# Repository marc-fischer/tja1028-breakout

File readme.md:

# TJA1028 Breakout board

This breakout board provides a simple method to use a TJA1028T LIN transceiver with any microcontroller or development board (ie. Arduino, NodeMCU)

## Picture of the Board

## Schematics

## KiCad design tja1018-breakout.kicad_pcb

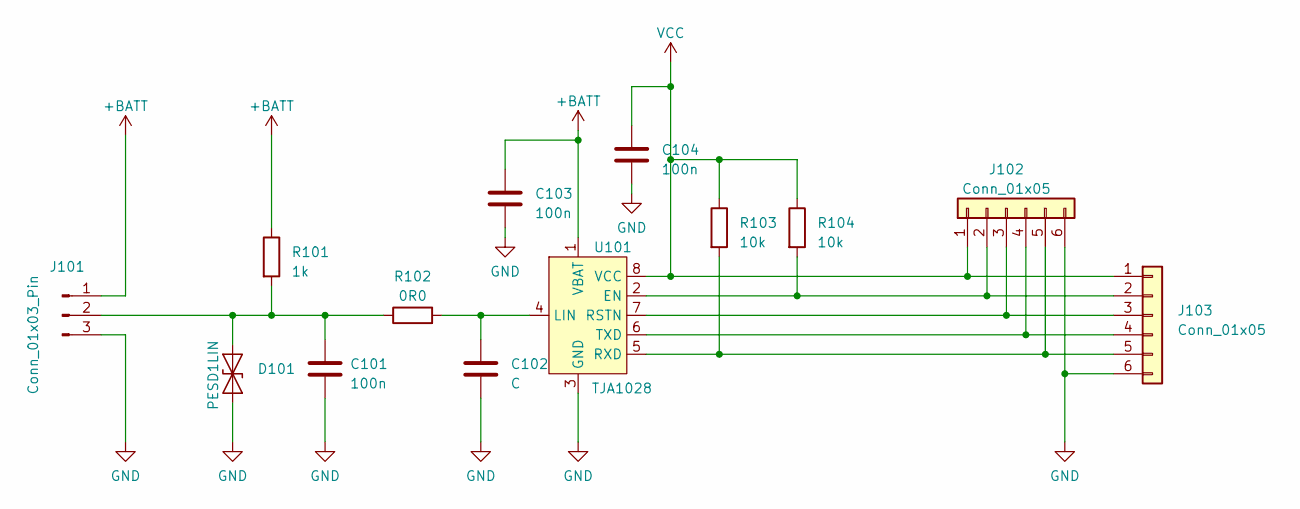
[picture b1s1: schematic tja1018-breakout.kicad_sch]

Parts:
C101, C103, C104: 100n; C_0603_1608Metric
C102: C; C_0603_1608Metric
D101: PESD1LIN; D_SMA-SMB_Universal_Handsoldering
J101: Conn_01x03_Pin; TerminalBlock_bornier-3_P5.08mm
J102, J103: Conn_01x05; PinHeader_1x06_P2.54mm_Vertical
R101: 1k; R_0603_1608Metric
R102: 0R0; R_0603_1608Metric
R103, R104: 10k; R_0603_1608Metric
U101: TJA1028; SO-8_3.9x4.9mm_P1.27mm

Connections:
+BATT: C103.1, J101.1, R101.1, U101.1 (VBAT)
GND: C101.2, C102.2, C103.2, C104.2, D101.1 (A1), J101.3, J102.6, J103.6, U101.3 (GND)
unnamed: C101.1, D101.2 (A2), J101.2, R101.2, R102.1
unnamed: J102.2, J103.2, R104.2, U101.2 (EN)
unnamed: J102.3, J103.3, U101.7 (RSTN)
unnamed: J102.4, J103.4, U101.6 (TXD)
unnamed: J102.5, J103.5, R103.2, U101.5 (RXD)
unnamed: C102.1, R102.2, U101.4 (LIN)
VCC: C104.1, J102.1, J103.1, R103.1, R104.1, U101.8 (VCC)

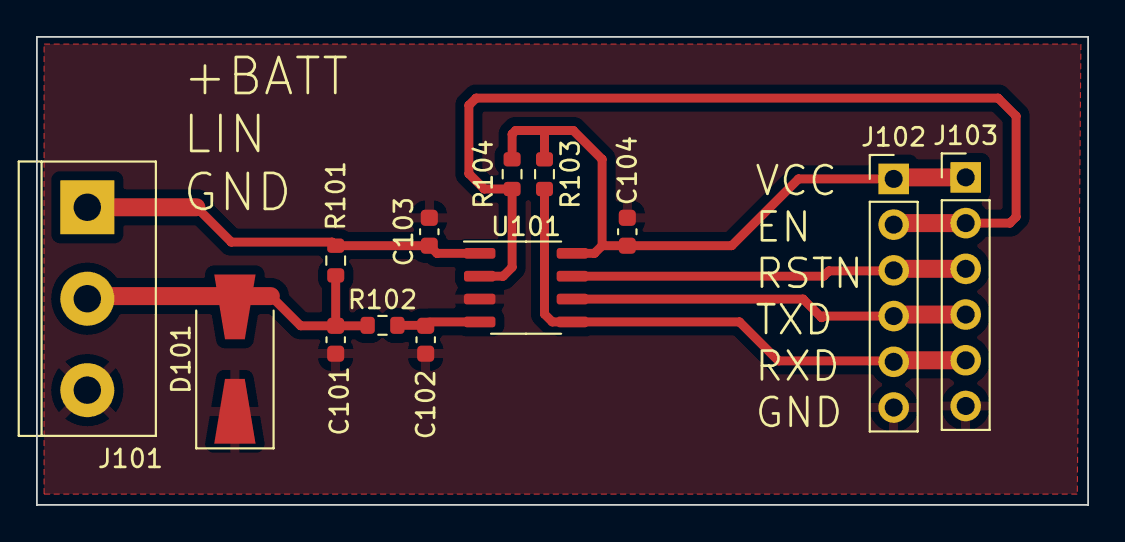
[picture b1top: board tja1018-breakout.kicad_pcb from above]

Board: 2 copper layers, 58.4 x 26.0 mm, 13 parts (0 on the bottom side), 9 nets.

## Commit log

2023-11-08 add readme
2023-11-08 add LICENSE
